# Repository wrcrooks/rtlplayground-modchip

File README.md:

# RTLPlayground mod chip

An RP2350 board inside SWTG024AS-V2.0 switches (MokerLink 2G040210GS, XikeStor SKS3200M-4GPY2XF) that
takes over management from the RTL8372's built-in 8051. The 8051 keeps only what has to run on it,
under a small bridge firmware, and tunnels the rest to the RP2350:

- chip init;
- SerDes and SFP upkeep;
- the CPU-port packet DMA;
- PHY, SerDes and flash access.

**Status:** Not tested as I haven't received the assembled PCBs yet.

The design, the link protocol, the pinouts and the mechanical constraints are in
[ARCHITECTURE.md](ARCHITECTURE.md). To test the firmware before the boards arrive, a Beetle RP2350 on jumper wires
stands in for the mod chip: [docs/beetle-test-rig.md](docs/beetle-test-rig.md).

| Path | What |
|---|---|
| `hardware/` | KiCad 10 schematic and 4-layer board, routed, with clean ERC and DRC. Also the board outline reaching headers T3, T8 and T5, a 1:1 print template, a DXF, photo overlays, STL/STEP for a printed fit check, JLCPCB production files, and the scripts that generate and check all of it. See [hardware/README.md](hardware/README.md) |
| `hardware/poe/` | A second board, 18.9 × 27.5 mm, for the MokerLink POE-2G040210GSM: on its T7 header, with wires to T9. Routed with a clean DRC, JLCPCB files included; its T7/T9 signal pins are still guesses. See [hardware/poe/README.md](hardware/poe/README.md) |
| `firmware/rp2350/` | The RP2350's application firmware in C (Pico SDK 2, lwIP): RTLPlayground's web UI, command line, IP stack, DHCP/DNS/NTP/syslog, STP/LACP/IGMP/LLDP and configuration, plus HTTPS, SSH, IPv6, SNMP, MQTT and Prometheus, 802.1X, multicast snooping, port protection, signed updates and a graphs dashboard, with RTLPlayground's modules compiled unchanged from a submodule. Builds and passes host tests; the base has run on a MokerLink through the Beetle rig, the newer features not on hardware yet. See [firmware/rp2350/README.md](firmware/rp2350/README.md) |
| `firmware/micropython/` | RP2350/RP2040 tools in MicroPython: `read_chip_id.py` reads the switch over T3, `bridge_link.py` is the host side of the bridge protocol, `bridge_host_test.py` talks to the bridge over T5, and `test_bridge_link.py` checks the protocol against the bridge's own frames |

The RP2350's application firmware is in `firmware/rp2350/`; it needs the submodule
(`git submodule update --init`).

## The bridge firmware

The 8051 side lives in RTLPlayground, on the `feat/modchip` branch of the fork:
[`modchip/bridge/`](https://github.com/wrcrooks/RTLPlayground/tree/feat/modchip/modchip/bridge). It shares
RTLPlayground's chip-level modules there. Build it from that repository's root:

```
make -f modchip/bridge/Makefile MACHINE=SWGT024_V2_0_UNMANAGED LAYOUT=compact   # MokerLink, 512 KiB
make -f modchip/bridge/Makefile MACHINE=SWGT024_V2_0_MANAGED                    # XikeStor, 2 MiB
make -f modchip/bridge/Makefile MACHINE=POE_2G040210GSM                         # MokerLink PoE, 2 MiB
```

The PoE switch's controller image goes into that last build with `tools/add_pse_image.py`. The RP2350
firmware for that board is `-DMODCHIP_BOARD=poe`.

## Roadmap

- **UniFi.** The switch as a UniFi switch: adopted by a UniFi Network controller, which sets its
  VLANs, port VLAN IDs, names and speeds, STP, isolation, storm control, egress limits and
  Etherlighting, and sees its clients and LLDP neighbours. In the firmware, tested against a
  controller in Docker and on the Beetle rig (`test/run_unifi_hw.py`). Next:
  port security, LAG and mirroring, which the controller refuses for the models the switch claims.
  See [firmware/rp2350/README.md](firmware/rp2350/README.md#unifi).
- **Port LED daughter board.** A small board on the mod chip with one WS2812B LED per port, chained,
  in the style of UniFi's Etherlighting. Each LED shows the colour of its port's VLAN, or the link
  speed, and blinks to locate a port, from the command line or from the controller's own locate and
  Etherlighting settings. The firmware side is done (`portled` commands, a PIO driver, colours tested
  on the host; see [firmware/rp2350/README.md](firmware/rp2350/README.md#port-led-board)), with no
  board to drive yet. Open questions:
  - **Placement.** Behind the front panel, over each port, with light pipes where the case has no
    window.
  - **Power (decided).** WS2812B LEDs from an MT3608 boost (JLCPCB basic part C84817) on the mod
    chip's 3.3 V, set to about 4.7 V (R1 68k, R2 10k; Vref 0.6 V). With an SS34 Schottky, a 10 µH
    inductor rated 2 A or more, 22 µF in and out, and 100 nF at each LED. No load switch: the
    firmware sends a dark frame before it lets the line go, and dark LEDs draw about 1 mA each. Full
    white is 60 mA per LED, 600 mA for ten; the firmware holds the LEDs to its budget (300 mA at
    first, 500 mA at most), about 1 A from 3.3 V at 500 mA. Still to find out: how much the switch's
    3.3 V rail can spare. On USB alone (AP2112K, 600 mA) the budget has to stay low.
  - **Signal (decided).** One spare RP2350 pin through 330 Ω, driven by a PIO state machine, no level
    shifter. The first LED gets its supply through a 1N4148W diode (about 4.0 V), so its input
    threshold (0.7 VDD, about 2.8 V) is under the RP2350's 3.3 V. Its output, at its own supply,
    drives the next LED, which is on the full 4.7 V.
  - **Connector.** The mod chip board has free GPIOs but no header for them yet: the next revision
    needs one for the data line, power and ground.

## Rebuilding the hardware

Needs the KiCad 10 flatpak and a checkout of kicad-agent-kit:

```
KAK=~/Desktop/Workspace/KiCad/kicad-agent-kit hardware/build.sh
```

This goes from the schematic through ERC, layout, Freerouting, DRC and the JLCPCB files to the STL/STEP.

## Tests

```
make -C firmware/rp2350/test PICO_SDK_PATH=...   # framing, a simulated bridge, TLS, SNMP
python3 firmware/micropython/test_bridge_link.py
python3 hardware/check_sch.py         # ERC, and every pin's net against hardware/expected-nets.json
```

## Credits

- [vDorst/rtl-rs](https://github.com/vDorst/rtl-rs), by vDorst: a Rust library and CLI for the RTL837x's
  slave interface. Its I²C transactions are the reference for the firmware's register access over T3
  (`t3 on`, `t3 test`), above all the write format, which RTLPlayground's notes left open. It also
  shows that the PHY, SerDes and SFP engines can be reached through plain registers.

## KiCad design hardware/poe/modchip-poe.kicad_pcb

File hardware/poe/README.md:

# Mod chip for the MokerLink POE-2G040210GSM

A second board for the PoE switch (PCB `2M-PCB49-V1.1`, RTL8372 with 2 MiB of flash): the same RP2350
circuit as the SWTG024AS-V2.0 board in `../`, cut down to what this switch offers and made as small as
it can be.

- **Size.** The board is 18.9 × 27.5 mm, with a corner cut away for the screw head beside T7. For
  comparison, the first board is 57 × 37 mm.
- **Placement.** It sits on T7 (the slave interface) beside the right SFP cage, on a male header
  soldered on its underside.
- **Wiring.** Four wires run from its pads J3 to T9 (the serial console), about 17 mm away.

**Status:** designed and routed with a clean DRC. Not built yet. **The T7 and T9 signal pins are
guesses.** Check them before ordering (see the end of this page).

| File | What |
|---|---|
| `modchip-poe.kicad_pcb`, `modchip-poe.kicad_pro` | KiCad 10 board. The outline is on Edge.Cuts and J1 is on the bottom side on T7's holes. The switch's parts are drawn on Dwgs.User and notes are on Cmts.User. The aux and grid origin is T7 pin 1 |
| `make_pcb.py`, `build.sh`, `modchip-poe.kicad_dru` | Layout and routing pipeline (as in `../`, with `../finish.py`), and JLCPCB's design rules |
| `modchip-poe.kicad_sch`, `schematic-poe.pdf` | Schematic, and a PDF of it |
| `make_sch.py` | Generates the schematic. It uses `../make_sch.py`'s generator and lists every pin's net |
| `check_sch.py`, `expected-nets.json` | ERC, plus KiCad's netlist compared pin by pin with the intended nets |
| `outline.py`, `overlay.jpg` | The outline, T7/T9/T10 and the obstacles in one place. Running it checks the clearances; `--photo` draws them on the photo |
| `lib/` | Footprints for U5 and L1, imported from LCSC, and L1's 3D model. U5 uses KiCad's Winbond USON-8 model |
| `production/` | JLCPCB files: Gerbers and drill zip, BOM, positions |
| `mechanical/` | STL and STEP of the assembled board, without J1/J3/J5, for a printed fit check |

Rebuild everything from the schematic to the production files with:

```
KAK=~/Desktop/Workspace/KiCad/kicad-agent-kit ./build.sh
python3 outline.py --photo headers.jpg   # RTLPlayground doc/devices/photos/2M-PCB49-V1.1/headers.jpg
```

## Circuit

The circuit is that of `../make_sch.py`, with these changes:

- **No USB.** Power comes from the switch's 3.3 V on T7 pin 4, through the LM66100 ideal diode U2.
  Programming and debug go over SWD (J5).
- **Bench power.** A debug probe can power the board on J5 pin 1; U2 keeps that supply out of the
  switch.
- **Flash.** U5 is a W25Q16JVUXIQ, 2 MiB in USON-8 2×3 mm, fitted with an RP2350A. The RP2354A has the
  same 2 MiB inside its package, but JLC has only a handful in stock. With an RP2354A in U1's place,
  leave U5 and C19 off.
- **Not on this board.** There is no T8-style GPIO header, since this switch has none, and no reset
  driver, since no reset point is known.
- **GPIO use is the same as the first board**, so the firmware's pin map holds:

  | GPIO | Use |
  |---|---|
  | GP0 / GP1 | UART0 |
  | GP11 / GP10 | I²C1 SCL / SDA |
  | GP9 / GP8 | T7 pins 5 / 6 |
  | GP22 | LED |
  | GP26 | Switch-power sense |

- **Series resistors and pull-ups.** Every line to the switch has 100 Ω in series. The I²C lines have
  4.7 kΩ pull-ups to the switch's 3.3 V.

| Pad | Signal |
|---|---|
| J1 (into T7) | 1 SCL, 2 GND, 3 SDA, 4 3.3 V from the switch, 5 GP9, 6 GP8 |
| J3 (wires to T9, pad n to pin n) | 1 the switch's U0TXD, 2 GND, 3 the switch's U0RXD, 4 not connected |
| J5 (SWD, 1.27 mm) | 1 3.3 V, 2 SWCLK, 3 GND, 4 SWDIO, 5 RUN |

`python3 check_sch.py` reports a clean ERC and all 168 pins on their intended nets (33 nets).

## Layout

The board has 4 layers, 1.0 mm thick:

| Layer | Use |
|---|---|
| F.Cu | Parts, signals and a GND pour |
| In1 | GND |
| In2 | +3V3 |
| B.Cu | Signals and a GND pour |

Only J1 is on the bottom side. `make_pcb.py` places these parts by hand:

- **U1** with GP0-GP11 facing J1.
- **The series resistors** in a column between J1 and U1.
- **The core regulator** (L1, CIN, COUT and the VREG_AVDD RC) above U1's VREG pins.
- **U5**, turned so that its SD0, SCLK, SD3 and VCC pins sit straight over U1's QSPI pins.
- **The crystal** in the corner below U1.
- **The SWD pads** along the right edge.

The other parts are auto-placed. Locked hand routes cover:

- VREG_LX and VREG_AVDD;
- the +3V3 trunk to CIN;
- the three straight QSPI lines and T7_P6;
- +1V1: a via at each DVDD pin and VREG_FB, joined on B.Cu by a cross through U1's exposed-pad vias.
  The footprint's B.Cu copper under the pad is removed for that.

Freerouting routes the rest, with analytics and telemetry off on its command line. The result has no
DRC errors or warnings and is fully connected.

## Ordering (`production/`)

- **Board.** 4 layers, 1.0 mm thick, 0.2 mm minimum via drill.
- **Assembly.** PCBA on the top side only: 41 parts, 18 BOM lines, every line with an LCSC number.
- **Parts.** All are in stock as of 2026-11-02. Basic parts throughout, except five Extended ones:

  | Part | LCSC | Stock |
  |---|---|---|
  | RP2350A | C42411118 | 4,697 |
  | W25Q16JVUXIQ | C2843335 | 450 |
  | ABM8 crystal | C20625731 | 8,774 |
  | LM66100 | C2869734 | 11,326 |
  | 3.3 µH inductor, FNR201610S3R3MT | C167673 | 1,380 |

- **The inductor.** The first board's AOTA-B201610S3R3 (C42411119, the part the RP2350 datasheet
  names) is down to 1 in stock. This board uses a shielded 2016 3.3 µH instead, rated 880 mA,
  plenty for the core supply. The first board's BOM needs the same substitute until the AOTA is back.
- **Not assembled.** J1 is a 1×6 2.54 mm male header, hand-soldered from below. J3 and J5 are bare
  pads.
- **Check in JLC's preview.** The rotation of U1, U5 (USON-8), U2, Y1 and L1.

## Before ordering a board

1. **Confirm T7's pinout.** Pin 2 GND and pin 4 3.3 V were measured on the switch. Pins 1/3
   (SCL/SDA) and 5/6 are copied from the 2M-PCB23-V3.1's T7. Check them with continuity, from T7 to the
   RTL8372's slave-interface pins, before ordering. If SCL and SDA are swapped, the RP2350's PIO can
   run I²C on either pin, so the board still works with a firmware change.
2. **Confirm T9's pinout.** Pin 1 TX and pin 3 RX are also a guess. Check with a USB-serial adapter at
   boot; a swap there only means crossing two wires.
3. **Keep T10 bare.** T10, three holes beside T7, sits under the board, so it must stay without pins.
4. **Check the fit.** The positions come from a photo, at 16.93 px/mm and about ±0.5 mm away from T7.
   The outline keeps at least 1.0 mm from the SFP cage, the screw head and the main PCB's edge.
   Print `mechanical/modchip-poe-no-headers.stl` or lay a 1:1 print of the outline on the switch.
5. **Measure the height.** The board sits on J1's plastic spacer, about 2.5 mm above the switch PCB.
   It is 1.0 mm thick and its tallest part reaches 1.1 mm above it. Trim J1's pins flush on top, and
   check the lid's clearance over T7.
6. **Firmware.** Build the RP2350's with `-DMODCHIP_BOARD=poe` (`firmware/rp2350/README.md`) and the
   8051 bridge with `MACHINE=POE_2G040210GSM`, plus the PoE image (RTLPlayground's
   `modchip/bridge/README.md`). Neither has run on this switch yet.

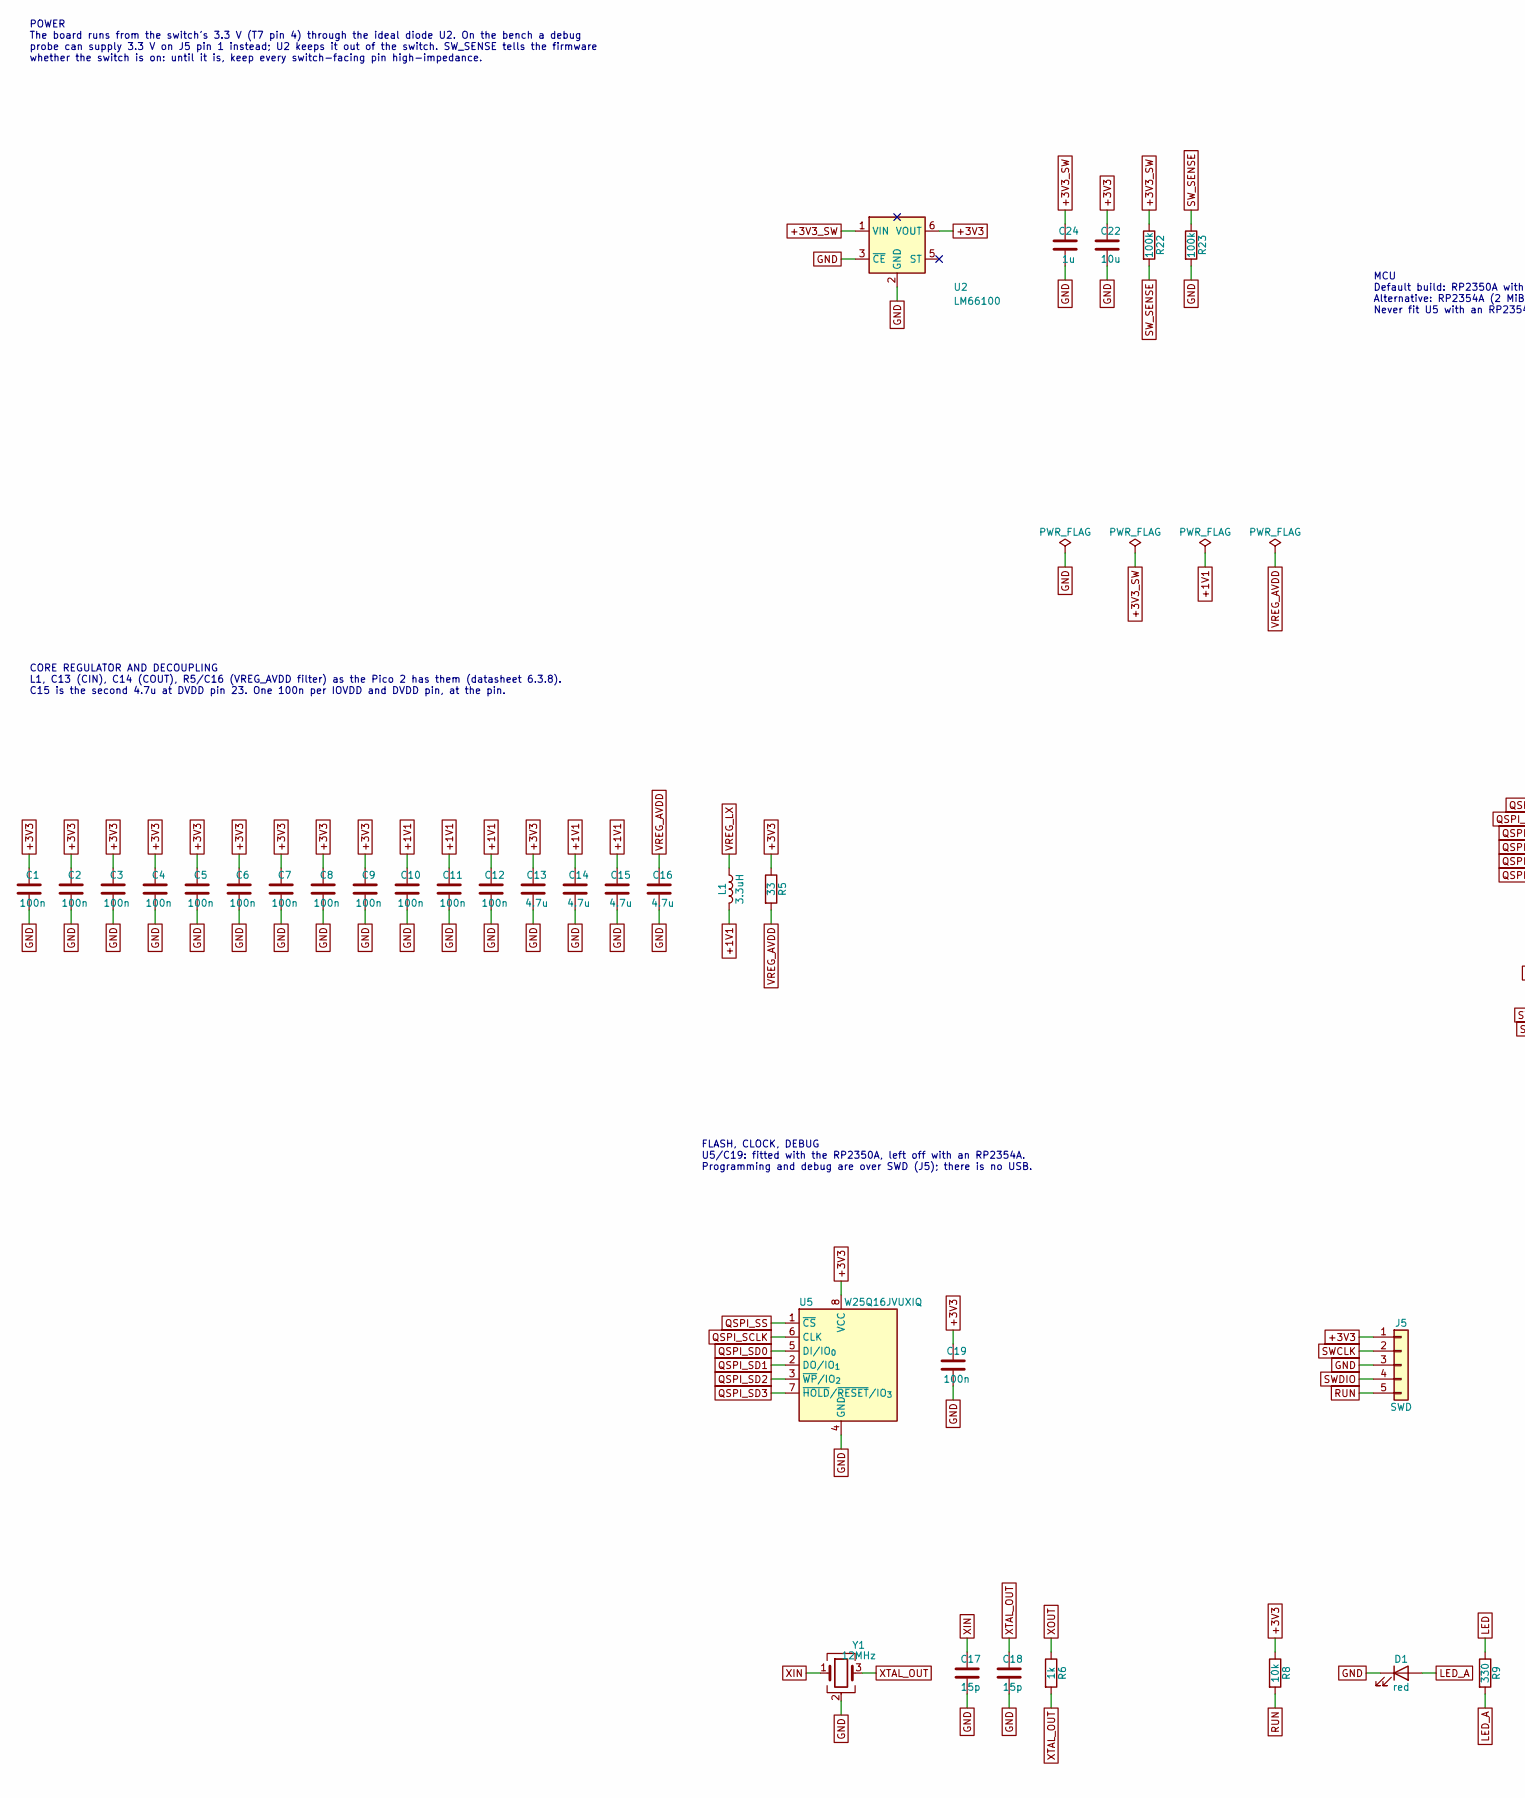
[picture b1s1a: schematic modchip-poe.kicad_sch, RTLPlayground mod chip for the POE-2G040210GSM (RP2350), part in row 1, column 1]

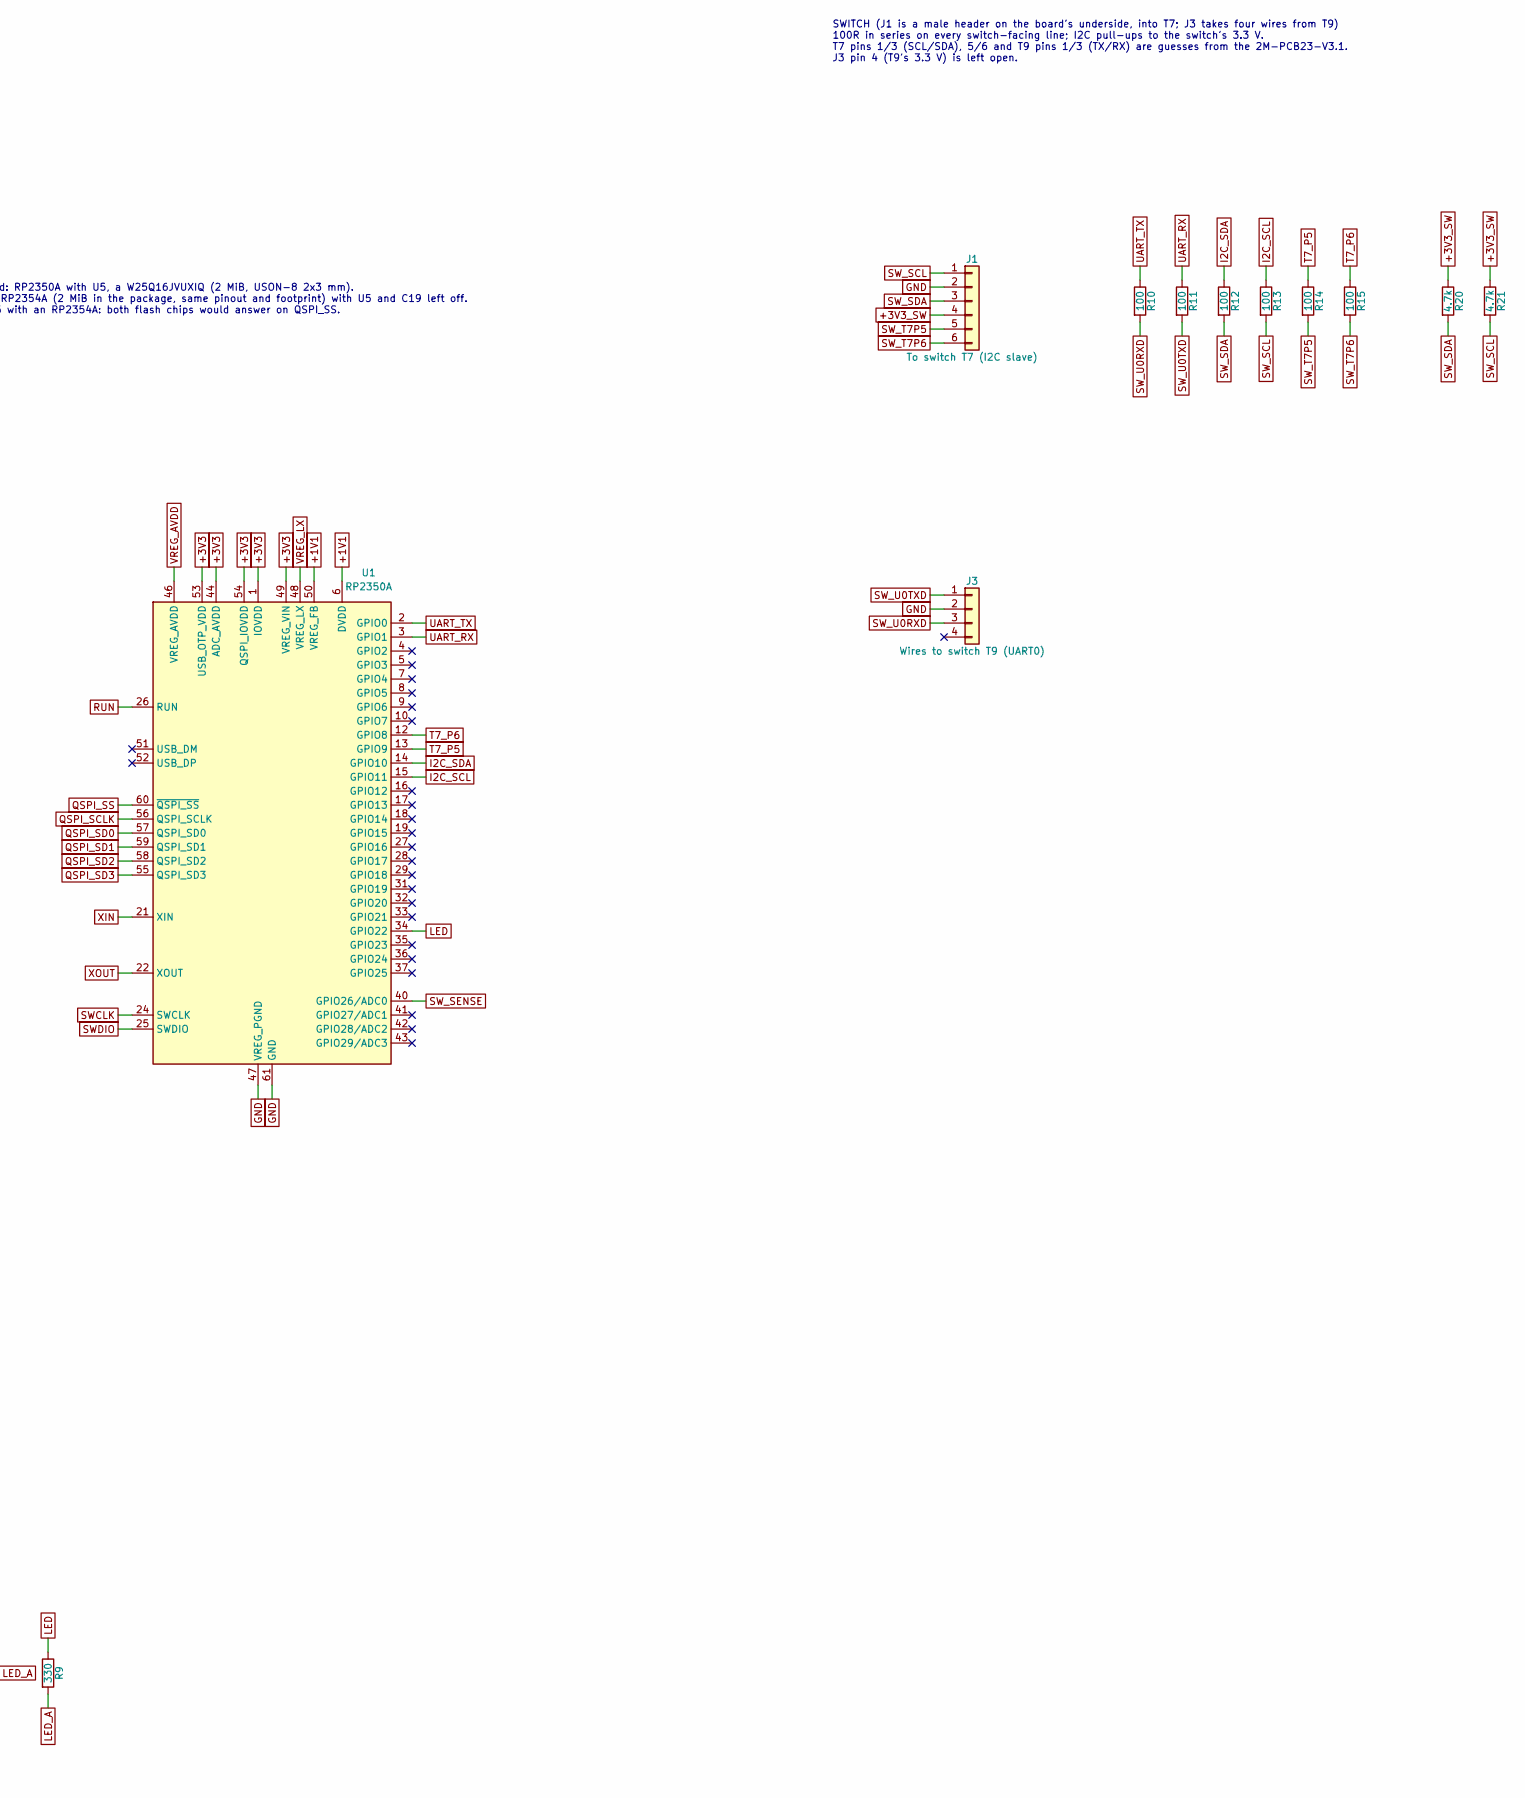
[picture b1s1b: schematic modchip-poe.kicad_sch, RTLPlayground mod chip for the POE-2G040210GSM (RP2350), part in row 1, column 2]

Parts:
C1, C2, C3, C4, C5, C6, C7, C8, C9, C10, C11, C12, C19: 100n; C_0402_1005Metric; LCSC C1525
C13, C14, C15, C16: 4.7u; C_0402_1005Metric; LCSC C23733
C17, C18: 15p; C_0402_1005Metric; LCSC C1548
C22: 10u; C_0603_1608Metric; LCSC C19702
C24: 1u; C_0402_1005Metric; LCSC C52923
D1: red; LED_0603_1608Metric; LCSC C2286
J1: To switch T7 (I2C slave); PinHeader_1x06_P2.54mm_Vertical
J3: Wires to switch T9 (UART0); PinHeader_1x04_P2.54mm_Vertical
J5: SWD; PinHeader_1x05_P1.27mm_Vertical
L1: 3.3uH; IND-SMD_L2.0-W1.6_FNR2016XXS; MPN Fenghua FNR201610S3R3MT, shielded 2016 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; LCSC C167673
R5: 33; R_0402_1005Metric; LCSC C25105
R6: 1k; R_0402_1005Metric; LCSC C11702
R8: 10k; R_0402_1005Metric; LCSC C25744
R9: 330; R_0402_1005Metric; LCSC C25104
R10, R11, R12, R13, R14, R15: 100; R_0402_1005Metric; LCSC C25076
R20, R21: 4.7k; R_0402_1005Metric; LCSC C25900
R22, R23: 100k; R_0402_1005Metric; LCSC C25741
U1: RP2350A; QFN-60-1EP_7x7mm_P0.4mm_EP3.4x3.4mm_ThermalVias; LCSC C42411118
U2: LM66100; SOT-363_SC-70-6; LCSC C2869734
U5: W25Q16JVUXIQ; USON-8_L3.0-W2.0-P0.50-BL-EP; LCSC C2843335
Y1: 12MHz; Crystal_SMD_3225-4Pin_3.2x2.5mm; MPN Abracon ABM8-272-T3: the RP2350 is tune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; LCSC C20625731

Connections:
+1V1: C10.1, C11.1, C12.1, C14.1, C15.1, L1.2, U1.6 (DVDD), U1.23 (DVDD), U1.39 (DVDD), U1.50 (VREG_FB)
+3V3: C1.1, C2.1, C3.1, C4.1, C5.1, C6.1, C7.1, C8.1, C9.1, C13.1, C19.1, C22.1, J5.1, R5.1, R8.1, U1.1 (IOVDD), U1.11 (IOVDD), U1.20 (IOVDD), U1.30 (IOVDD), U1.38 (IOVDD), U1.44 (ADC_AVDD), U1.45 (IOVDD), U1.49 (VREG_VIN), U1.53 (USB_OTP_VDD), U1.54 (QSPI_IOVDD), U2.6 (VOUT), U5.8 (VCC)
+3V3_SW: C24.1, J1.4, R20.1, R21.1, R22.1, U2.1 (VIN)
GND: C1.2, C2.2, C3.2, C4.2, C5.2, C6.2, C7.2, C8.2, C9.2, C10.2, C11.2, C12.2, C13.2, C14.2, C15.2, C16.2, C17.2, C18.2, C19.2, C22.2, C24.2, D1.1 (K), J1.2, J3.2, J5.3, R23.2, U1.47 (VREG_PGND), U1.61 (GND), U2.2 (GND), U2.3 (~CE), U5.4 (GND), Y1.2 (G), Y1.4 (G)
I2C_SCL: R13.1, U1.15 (GPIO11)
I2C_SDA: R12.1, U1.14 (GPIO10)
LED: R9.1, U1.34 (GPIO22)
LED_A: D1.2 (A), R9.2
QSPI_SCLK: U1.56 (QSPI_SCLK), U5.6 (CLK)
QSPI_SD0: U1.57 (QSPI_SD0), U5.5 (DI/IO_{0})
QSPI_SD1: U1.59 (QSPI_SD1), U5.2 (DO/IO_{1})
QSPI_SD2: U1.58 (QSPI_SD2), U5.3 (~WP/IO_{2})
QSPI_SD3: U1.55 (QSPI_SD3), U5.7 (~HOLD/~RESET/IO_{3})
QSPI_SS: U1.60 (~QSPI_SS), U5.1 (~CS)
RUN: J5.5, R8.2, U1.26 (RUN)
SWCLK: J5.2, U1.24 (SWCLK)
SWDIO: J5.4, U1.25 (SWDIO)
SW_SCL: J1.1, R13.2, R21.2
SW_SDA: J1.3, R12.2, R20.2
SW_SENSE: R22.2, R23.1, U1.40 (GPIO26/ADC0)
SW_T7P5: J1.5, R14.2
SW_T7P6: J1.6, R15.2
SW_U0RXD: J3.3, R10.2
SW_U0TXD: J3.1, R11.2
T7_P5: R14.1, U1.13 (GPIO9)
T7_P6: R15.1, U1.12 (GPIO8)
UART_RX: R11.1, U1.3 (GPIO1)
UART_TX: R10.1, U1.2 (GPIO0)
VREG_AVDD: C16.1, R5.2, U1.46 (VREG_AVDD)
VREG_LX: L1.1, U1.48 (VREG_LX)
XIN: C17.1, U1.21 (XIN), Y1.1
XOUT: R6.1, U1.22 (XOUT)
XTAL_OUT: C18.1, R6.2, Y1.3

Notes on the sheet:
POWER The board runs from the switch's 3.3 V (T7 pin 4) through the ideal diode U2. On the bench a debug probe can supply 3.3 V on J5 pin 1 instead; U2 keeps it out of the switch. SW_SENSE tells the firmware whether the switch is on: until it is, keep every switch-facing pin high-impedance.
MCU Default build: RP2350A with U5, a W25Q16JVUXIQ (2 MiB, USON-8 2x3 mm). Alternative: RP2354A (2 MiB in the package, same pinout and footprint) with U5 and C19 left off. Never fit U5 with an RP2354A: both flash chips would answer on QSPI_SS.
FLASH, CLOCK, DEBUG U5/C19: fitted with the RP2350A, left off with an RP2354A. Programming and debug are over SWD (J5); there is no USB.
SWITCH (J1 is a male header on the board's underside, into T7; J3 takes four wires from T9) 100R in series on every switch-facing line; I2C pull-ups to the switch's 3.3 V. T7 pins 1/3 (SCL/SDA), 5/6 and T9 pins 1/3 (TX/RX) are guesses from the 2M-PCB23-V3.1. J3 pin 4 (T9's 3.3 V) is left open.
CORE REGULATOR AND DECOUPLING L1, C13 (CIN), C14 (COUT), R5/C16 (VREG_AVDD filter) as the Pico 2 has them (datasheet 6.3.8). C15 is the second 4.7u at DVDD pin 23. One 100n per IOVDD and DVDD pin, at the pin.

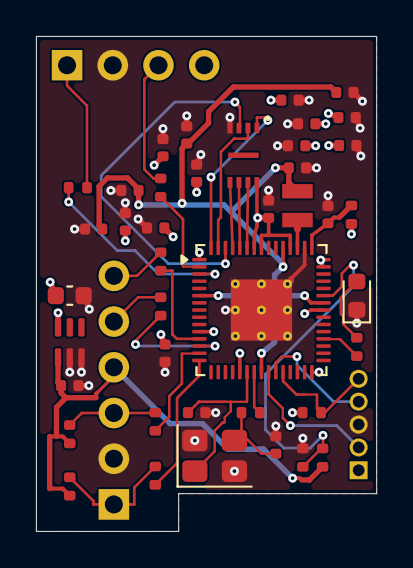
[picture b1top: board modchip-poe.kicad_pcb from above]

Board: 4 copper layers, 18.9 x 27.5 mm, 44 parts (1 on the bottom side), 33 nets.

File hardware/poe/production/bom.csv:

Designator,Footprint,Quantity,Value,LCSC Part #
"C1, C10, C11, C12, C19, C2, C3, C4, C5, C6, C7, C8, C9",0402,13,100n,C1525
"C13, C14, C15, C16",0402,4,4.7u,C23733
"C17, C18",0402,2,15p,C1548
C22,0603,1,10u,C19702
C24,0402,1,1u,C52923
D1,0603,1,red,C2286
L1,IND-SMD_L2.0-W1.6_FNR2016XXS,1,3.3uH,C167673
"R10, R11, R12, R13, R14, R15",0402,6,100,C25076
"R20, R21",0402,2,4.7k,C25900
"R22, R23",0402,2,100k,C25741
R5,0402,1,33,C25105
R6,0402,1,1k,C11702
R8,0402,1,10k,C25744
R9,0402,1,330,C25104
U1,QFN-60-1EP_7x7mm_P0.4mm_EP3.4x3.4mm_ThermalVias,1,RP2350A,C42411118
U2,SOT-363_SC-70-6,1,LM66100,C2869734
U5,USON-8_L3.0-W2.0-P0.50-BL-EP,1,W25Q16JVUXIQ,C2843335
Y1,Crystal_SMD_3225-4Pin_3.2x2.5mm,1,12MHz,C20625731

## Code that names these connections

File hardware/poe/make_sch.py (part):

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
GPIO use matches the first board, so the firmware's pin map holds: GP0/GP1 UART0, GP11/GP10 I2C1
SCL/SDA, GP9/GP8 to T7 pins 5/6, GP22 LED, GP26 the switch-power sense. If T7's or T9's pins
turn out swapped, the RP2350's PIO can run I2C and UART on either pin.

  flatpak run --command=python3 org.kicad.KiCad make_sch.py
  flatpak run --command=kicad-cli org.kicad.KiCad sch upgrade modchip-poe.kicad_sch
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    # ---- Power: the switch's 3.3 V through an ideal diode, and the sense divider
    ox, oy = 10, 18
    s.text("POWER\nThe board runs from the switch's 3.3 V (T7 pin 4) through the ideal diode U2. On the bench a debug\n"
           "probe can supply 3.3 V on J5 pin 1 instead; U2 keeps it out of the switch. SW_SENSE tells the firmware\n"
           "whether the switch is on: until it is, keep every switch-facing pin high-impedance.",
           (ox, oy - 8))
    s.part("U2", "Power_Management:LM66100DCK", "LM66100", (ox + 62, oy + 8),
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        "~{QSPI_SS}": "QSPI_SS", "QSPI_SCLK": "QSPI_SCLK", "QSPI_SD0": "QSPI_SD0", "QSPI_SD1": "QSPI_SD1",
        "QSPI_SD2": "QSPI_SD2", "QSPI_SD3": "QSPI_SD3",
        # GP0..GP11 are U1's left side, which faces J1: GP8..GP11 meet T7 pins 6, 5, 3, 1 in order
        "GPIO0": "UART_TX", "GPIO1": "UART_RX", "GPIO11": "I2C_SCL", "GPIO10": "I2C_SDA",
        "GPIO9": "T7_P5", "GPIO8": "T7_P6",
        "GPIO22": "LED", "GPIO26/ADC0": "SW_SENSE",
        **{"GPIO%d" % n: None for n in (2, 3, 4, 5, 6, 7, 12, 13, 14, 15, 16, 17, 18, 19, 20, 21, 23, 24, 25)},
        "GPIO27/ADC1": None, "GPIO28/ADC2": None, "GPIO29/ADC3": None,
    })
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
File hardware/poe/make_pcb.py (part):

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PLACEMENT = {
    "U1": (U1_AT[0], U1_AT[1], 0),
    # core regulator above U1's top-right pins (46 AVDD, 47 PGND, 48 LX, 49 VIN, 50 FB):
    # L1 straight above LX, CIN by VIN, the VREG_AVDD RC by pin 46, COUT beyond L1
    "L1": (10.2, -16.6, 90), "C13": (8.6, -16.4, 90), "C16": (11.9, -16.1, 90), "R5": (13.2, -16.1, 90),
    "C14": (10.2, -18.7, 0),
    # flash above U1, turned so its pins 5..8 (SD0, SCLK, SD3, VCC) sit over U1's 57..54; SS, SD1
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    # +1V1: DVDD pins 6 (left), 23 (bottom), 39 (right) and VREG_FB 50 (top) each drop a via between
    # the pad ring and the exposed pad, joined on B.Cu by a cross through the exposed pad's thermal
    # vias (its B.Cu copper is removed in build()). That leaves room beside them for the plane vias
    # of the +3V3 pins 20 and 38, which can't go outwards: XIN and SW_SENSE leave there.
    y = U1_AT[1] - 0.8
    xc = U1_AT[0] + 0.725
    vias = {6: (U1_AT[0] - 2.4, y), 23: rel(0.0, 2.4), 39: (U1_AT[0] + 2.4, y), 50: rel(1.2, -2.4)}
    for pin, v in vias.items():
        # pin 39 inwards first, clear of SW_SENSE's pad below it
        r.route("+1V1", [("U1", pin)] + ([(U1_AT[0] + 2.75, U1_AT[1] - 0.4)] if pin == 39 else []) + [v], width=0.2)
        r.via("+1V1", v, drill=VIA[1], size=VIA[0])
    r.route("+1V1", [vias[6], vias[39]], width=0.3, layer="B.Cu")
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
